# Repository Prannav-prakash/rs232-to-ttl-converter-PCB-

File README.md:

# RS232-to-ttl-converter-PCB
RS232 to TTL interface PCB for connecting an Inertial Labs INS-DU to a Cube Orange Plus flight controller at 921600 bps.

# Overview

This project implements a dedicated RS232-to-TTL interface board for communication between an Inertial Labs INS-DU navigation system and a Cube Orange Plus flight controller.

The board performs RS232 level shifting using the MAX3232E transceiver while also providing a power passthrough interface from an external BEC to the INS-DU. The design supports high-speed serial communication at up to 921600 baud and was developed using KiCad.

# Features
RS232 to TTL voltage level conversion using MAX3232
Compatible with Cube Orange Plus flight controller
Compatible with Inertial Labs INS-DU navigation system
Supports serial communication up to 921600 baud
External BEC power passthrough to INS-DU

# System Architecture

Cube Orange Plus UART (TTL)

↓

MAX3232E Level Shifter

↓

INS-DU RS232 Interface

Power for the INS-DU is supplied independently through an external BEC and routed through the PCB.

# Hardware Components
Integrated Circuits
MAX3232E RS232 Transceiver
Passive Components
Charge pump capacitors required by MAX3232
Power supply decoupling capacitor
Connectors
Cube Orange Plus Interface Connector
INS-DU Interface Connector
BEC Power Input Connector

# Repository Contents
KiCad Schematic Files

KiCad PCB Layout Files

Custom Symbols

Custom Footprints

3D Models

Documentation

Images
# PCB layout

# schematic 

# 3D view

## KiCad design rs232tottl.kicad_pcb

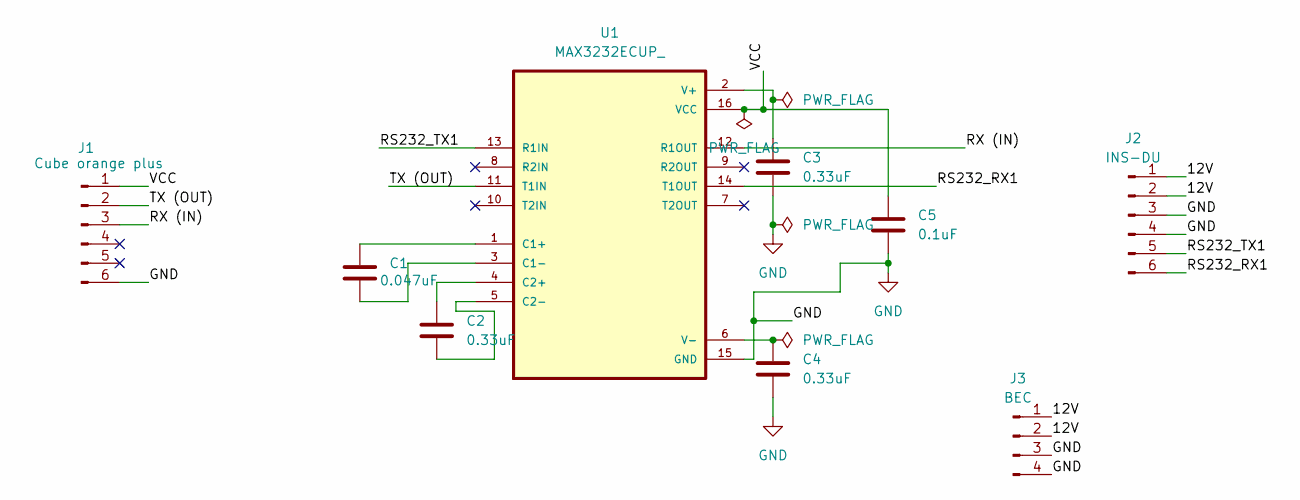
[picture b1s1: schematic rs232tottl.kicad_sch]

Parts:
C1: 0.047uF; C_0402_1005Metric
C2, C3, C4: 0.33uF; C_0402_1005Metric
C5: 0.1uF; C_0402_1005Metric
J1: Cube orange plus; JST_GH_BM06B-GHS-TBT_1x06-1MP_P1.25mm_Vertical
J2: INS-DU; JST_GH_BM06B-GHS-TBT_1x06-1MP_P1.25mm_Vertical
J3: BEC; JST_GH_BM04B-GHS-TBT_1x04-1MP_P1.25mm_Vertical
U1: MAX3232ECUP_; TSSOP-16_4.4x5mm_P0.65mm

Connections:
/12V: J2.1, J2.2, J3.1, J3.2
/RS232_RX1: J2.6, U1.14 (T1OUT)
/RS232_TX1: J2.5, U1.13 (R1IN)
/RX (IN): J1.3, U1.12 (R1OUT)
/TX (OUT): J1.2, U1.11 (T1IN)
/VCC: C5.1, J1.1, U1.16 (VCC)
GND: C3.2, C4.2, C5.2, J1.6, J2.3, J2.4, J3.3, J3.4, U1.15 (GND)
unnamed: C1.1, U1.1 (C1+)
unnamed: C1.2, U1.3 (C1-)
unnamed: C2.1, U1.4 (C2+)
unnamed: C2.2, U1.5 (C2-)
unnamed: C3.1, U1.2 (V+)
unnamed: C4.1, U1.6 (V-)

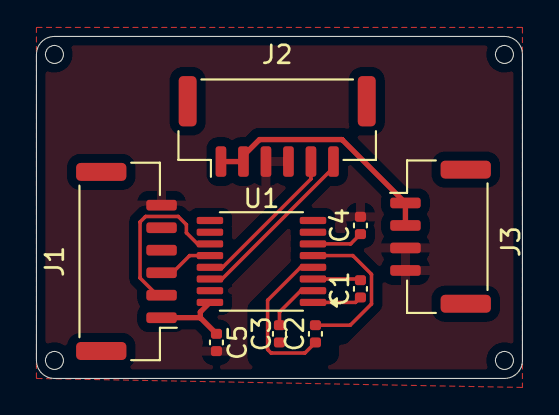
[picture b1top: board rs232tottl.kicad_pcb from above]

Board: 2 copper layers, 27.0 x 19.0 mm, 9 parts (0 on the bottom side), 13 nets.

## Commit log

2026-06-22 KiCad project files
2026-06-22 KiCad files
2026-06-22 Images of the board
2026-06-22 Enhance README with project details and images
    Expanded the README.md file to include an overview, features, system architecture, hardware components, repository contents, and images related to the RS232-to-TTL converter PCB.
